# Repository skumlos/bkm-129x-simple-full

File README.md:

A full sized version of the BKM-129X compatible board

Revision D

Should be able to be created at ~$40, with the ADG1611BRUZ being the most expensive component.
Note that DG1411EEQ is pin-compatible with a slighly higher Ron.

This requires an Arduino Nano v3 *or* the ATMEGA328PB mounted, which is then loaded with the
latest BKM-129X-MCU code from https://github.com/skumlos/bkm-129x-mcu

The has 4 switches to be able to turn internal 75 Ohm termination on out pass signal through to the output BNCs. You 
can choose to set all switches down, and then terminate with external termination resistors. If you wish to omit the
switches altogther, bridge the two pins bottom left of each switch (when viewed component side, BNCs to left). 
A 0 Ohm 0805 should be able to reach here I guess.

Connections from top to bottom when viewing component side, with BNCs to the left:
               _______________________________________
            __| _                                     |
Y/G IN     |___|_|                                    |
            __| _                                     |
Y/G OUT    |___|_|                                   _|
            __| _                                   | |
B-Y/B IN   |___|_|                                  | |
            __| _                                   | |
B-Y/B OUT  |___|_|                                  | |
            __| _                                   | |
R-Y/R IN   |___|_|                                  | |
            __| _                                   | |
R-Y/R OUT  |___|_|                                  | |
            __| _                                   |_|
SYNC IN    |___|_|                                    |
            __| _                                     |
SYNC OUT   |___|_|                                    |
              |_______________________________________|

Just like the original BKM-129X.

For more information go to https://immerhax.com/?p=422

You are welcome to clone, produce and sell hardware based on this. Please keep changes and so on open source.

Cool kids give credit where due.

---------

Programming the onboard ATMEGA328PB is a little different than when using a pre-made Arduino board.
The reason for this is that the fuses of the ATMEGA aren't set when the MCU leaves the factory.
Thus to program it, you will need ATMEGA328PB support in the Arduino IDE. The easiest way is to
install the MiniCore board support package (through the Boards Manager), for installation
check the "How to install" at https://github.com/MCUdude/MiniCore.
When MiniCore is available,  select the ATMEGA328 under MiniCore in the board menu, then select
"External 16 MHz" in Clock, disable BOD, select ATMEGA328PB in Variant, select No bootloader.
Then press "Burn bootloader" (assuming your programmer and so on is already setup). This will
program the fuses. Last, upload the sketch by pressing "Upload using programmer". If you don't
do this, nothing will work, because the MCU won't know how to use the external clock and so on.

---------

Should be compatible with basically all monitors that accept the original BKM-129X

Check the MCU code for verified compatibility.

---------

Board revision history:

D: Change hole size in backplane connector to accomodate larger pin sizes,
   support 1117 LDOs, change to Kicad 5 footprints, general cleanup

C: Fixed THS7374 filter bypass.

B: Added onboard MCU option

A: Initial version

---------

Copyright © 2022 Martin Hejnfelt <martin@hejnfelt.com>
This work is free. You can redistribute it and/or modify it under the
terms of the Do What The Fuck You Want To Public License, Version 2,
as published by Sam Hocevar. See the LICENSE file for more details.

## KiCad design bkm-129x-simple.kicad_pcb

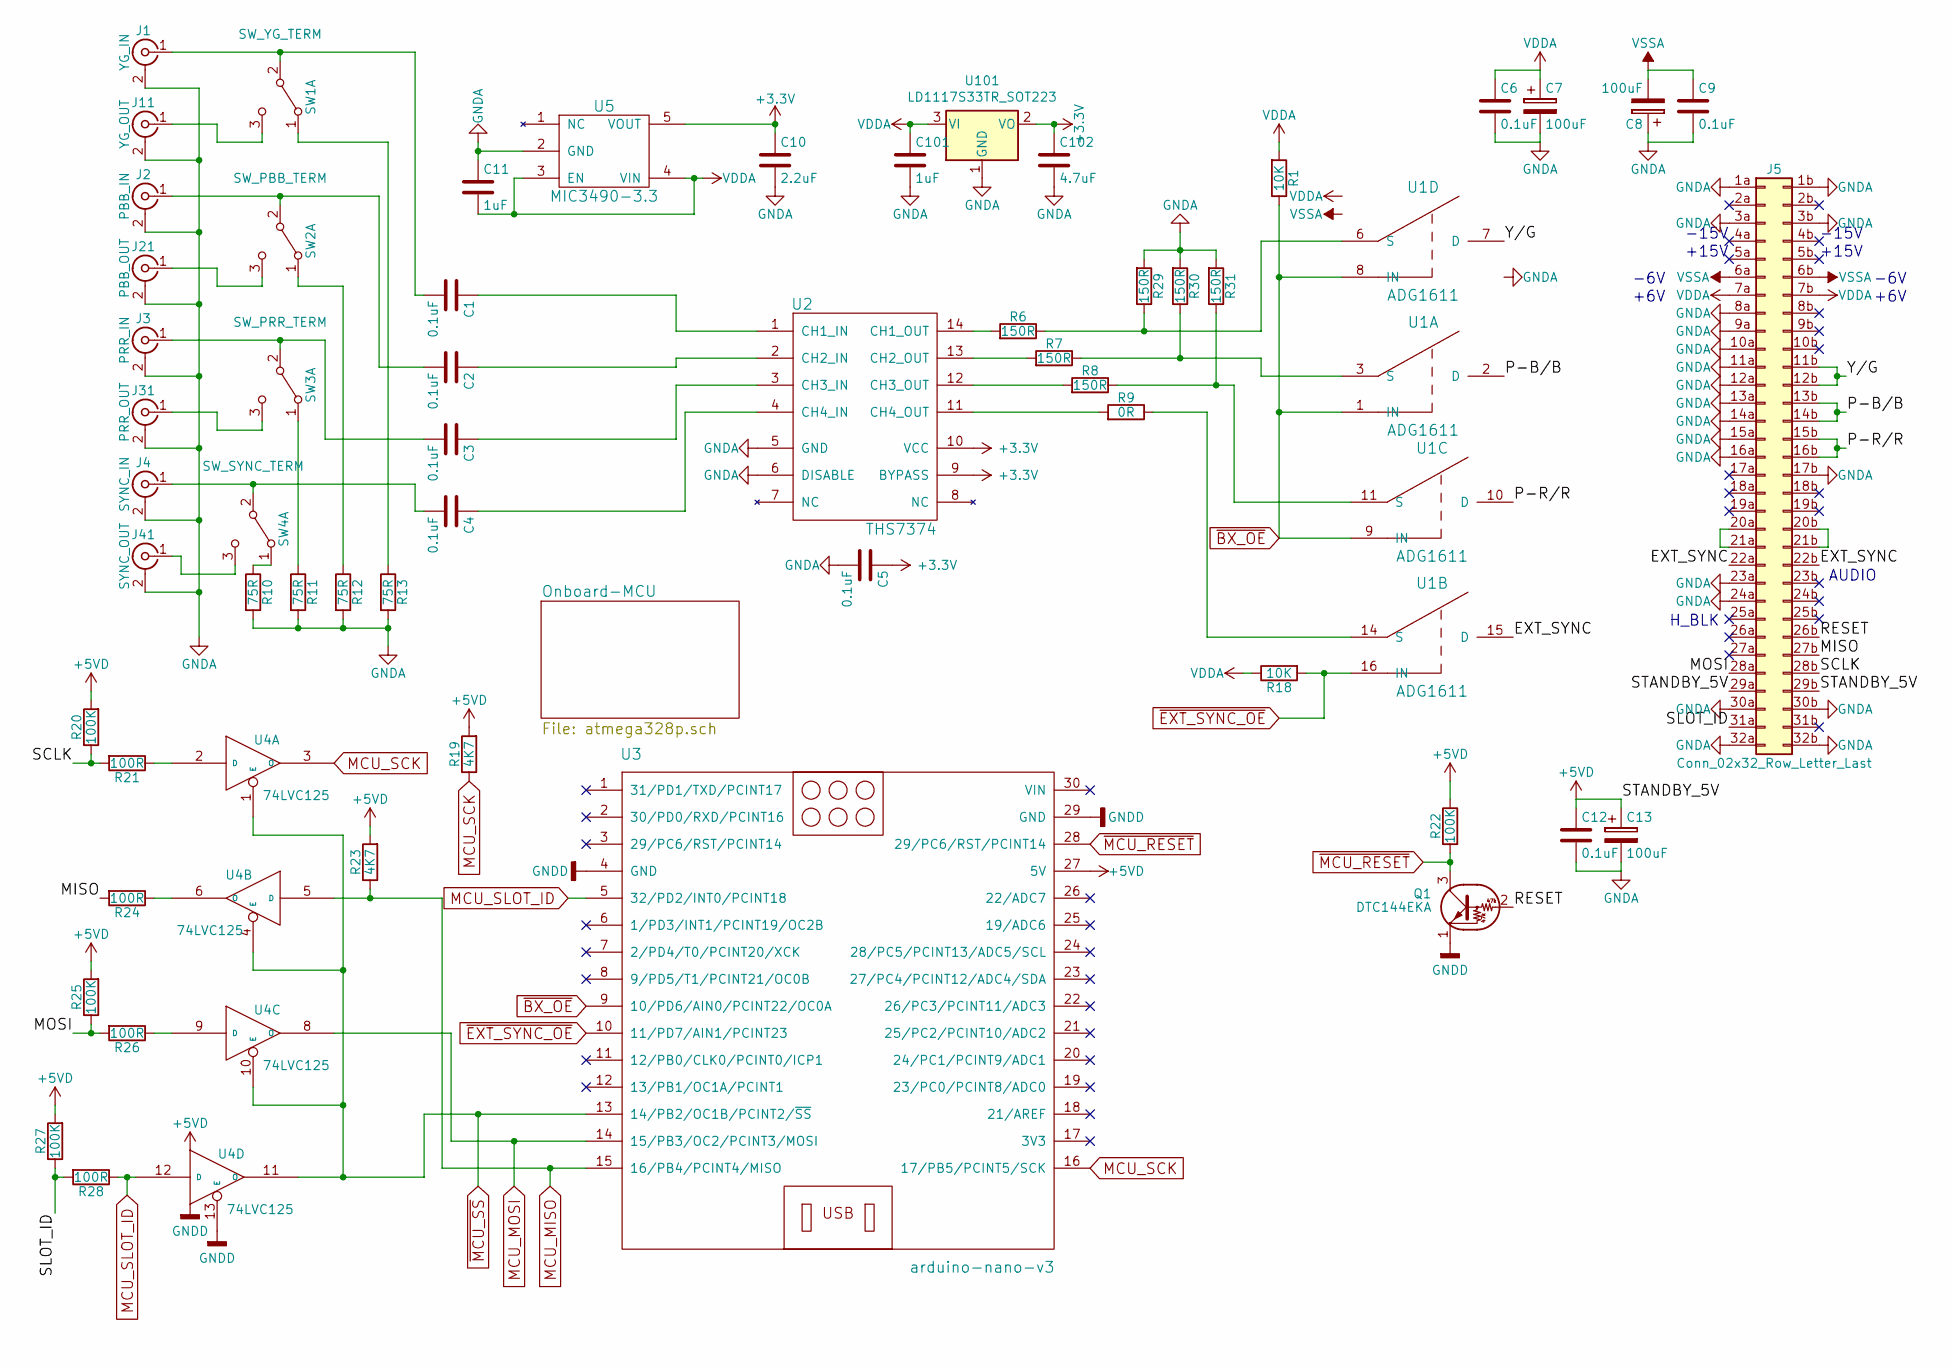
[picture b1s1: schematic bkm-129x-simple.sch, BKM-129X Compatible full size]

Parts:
C1, C2, C3, C4, C5, C6, C9, C12: 0.1uF; C_0805_2012Metric_Pad1.18x1.45mm_HandSolder
C7, C8, C13: 100uF; CP_Elec_6.3x5.3
C10: 2.2uF; C_0805_2012Metric_Pad1.18x1.45mm_HandSolder
C11, C101: 1uF; C_0805_2012Metric_Pad1.18x1.45mm_HandSolder
C102: 4.7uF; C_0805_2012Metric_Pad1.18x1.45mm_HandSolder
J1: YG_IN; BNC-THT
J2: PBB_IN; BNC-THT
J3: PRR_IN; BNC-THT
J4: SYNC_IN; BNC-THT
J5: Conn_02x32_Row_Letter_Last; STANDARD-PIN-64P-RA
J11: YG_OUT; BNC-THT
J21: PBB_OUT; BNC-THT
J31: PRR_OUT; BNC-THT
J41: SYNC_OUT; BNC-THT
Q1: DTC144EKA; SC-59_Handsoldering
R1, R18: 10K; R_0805_2012Metric_Pad1.20x1.40mm_HandSolder
R6, R7, R8, R29, R30, R31: 150R; R_0805_2012Metric_Pad1.20x1.40mm_HandSolder
R9: 0R; R_0805_2012Metric_Pad1.20x1.40mm_HandSolder
R10, R11, R12, R13: 75R; R_0805_2012Metric_Pad1.20x1.40mm_HandSolder
R19, R23: 4K7; R_0805_2012Metric_Pad1.20x1.40mm_HandSolder
R20, R22, R25, R27: 100K; R_0805_2012Metric_Pad1.20x1.40mm_HandSolder
R21, R24, R26, R28: 100R; R_0805_2012Metric_Pad1.20x1.40mm_HandSolder
SW1: SW_YG_TERM; JS202011SCQN
SW2: SW_PBB_TERM; JS202011SCQN
SW3: SW_PRR_TERM; JS202011SCQN
SW4: SW_SYNC_TERM; JS202011SCQN
U1: ADG1611; TSSOP-16_4.4x5mm_P0.65mm
U2: THS7374; TSSOP-14_4.4x5mm_P0.65mm
U3: arduino-nano-v3
U4: 74LVC125; TSSOP-14_4.4x5mm_P0.65mm
U5: MIC3490-3.3; SOT-23-5_HandSoldering
U101: LD1117S33TR_SOT223; SOT-223-3_TabPin2

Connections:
+3V3: C5.1, C10.1, C102.1, U2.9 (BYPASS), U2.10 (VCC), U5.5 (VOUT), U101.2 (VO)
+5VD: C12.1, C13.1, J5.29a, J5.29b, R19.2, R20.2, R22.1, R23.2, R25.2, R27.2, U3.27 (5V), U4.14 (VCC); also elsewhere on the board
/EXT_SYNC: J5.22a, J5.22b, U1.15 (D)
/MISO: J5.27b, R24.2
/MOSI: J5.28a, R25.1, R26.2
/P-B/B: J5.13b, J5.14b, U1.2 (D)
/P-R/R: J5.15b, J5.16b, U1.10 (D)
/RESET: J5.26b, Q1.2 (B)
/SCLK: J5.28b, R20.1, R21.2
/SLOT_ID: J5.31a, R27.1, R28.2
/Y/G: J5.11b, J5.12b, U1.7 (D)
MCU_MISO: R23.1, U3.15 (16/PB4/PCINT4/MISO), U4.5 (D); also elsewhere on the board
MCU_MOSI: U3.14 (15/PB3/OC2/PCINT3/MOSI), U4.8 (O); also elsewhere on the board
MCU_SCK: R19.1, U3.16 (17/PB5/PCINT5/SCK), U4.3 (O); also elsewhere on the board
MCU_SLOT_ID: R28.1, U3.5 (32/PD2/INT0/PCINT18), U4.12 (D); also elsewhere on the board
unnamed: C1.1, U2.1 (CH1_IN)
unnamed: C1.2, J1.1 (In), SW1.2 (B)
unnamed: C2.1, U2.2 (CH2_IN)
unnamed: C2.2, J2.1 (In), SW2.2 (B)
unnamed: C3.1, U2.3 (CH3_IN)
unnamed: C3.2, J3.1 (In), SW3.2 (B)
unnamed: C4.1, U2.4 (CH4_IN)
unnamed: C4.2, J4.1 (In), SW4.2 (B)
unnamed: J5.20a, J5.21a
unnamed: J5.20b, J5.21b
unnamed: J11.1 (In), SW1.3 (C)
unnamed: J21.1 (In), SW2.3 (C)
unnamed: J31.1 (In), SW3.3 (C)
unnamed: J41.1 (In), SW4.3 (C)
unnamed: R6.2, U2.14 (CH1_OUT)
unnamed: R7.2, U2.13 (CH2_OUT)
unnamed: R8.2, U2.12 (CH3_OUT)
unnamed: R9.1, U1.14 (S)
unnamed: R9.2, U2.11 (CH4_OUT)
unnamed: R10.1, SW4.1 (A)
unnamed: R11.1, SW3.1 (A)
unnamed: R12.1, SW2.1 (A)
unnamed: R13.1, SW1.1 (A)
unnamed: R21.1, U4.2 (D)
unnamed: R24.1, U4.6 (O)
unnamed: R26.1, U4.9 (D)
unnamed: R6.1, R29.1, U1.6 (S)
unnamed: R7.1, R30.1, U1.3 (S)
unnamed: R8.1, R31.1, U1.11 (S)
VDD: C6.1, C7.1, C11.2, C101.1, J5.7a, J5.7b, R1.2, R18.1, U1.13 (VDD), U5.3 (EN), U5.4 (VIN), U101.3 (VI)
VSS: C8.2, C9.1, J5.6a, J5.6b, U1.4 (VSS)
~BX_OE: R1.1, U1.1 (IN), U1.8 (IN), U1.9 (IN), U3.9 (10/PD6/AIN0/PCINT22/OC0A); also elsewhere on the board
~EXT_SYNC_OE: R18.2, U1.16 (IN), U3.10 (11/PD7/AIN1/PCINT23); also elsewhere on the board
~MCU_RESET: Q1.3 (C), R22.2, U3.28 (29/PC6/RST/PCINT14); also elsewhere on the board
~MCU_SS: U3.13 (14/PB2/OC1B/PCINT2/~SS), U4.1 (E), U4.4 (E), U4.10 (E), U4.11 (O); also elsewhere on the board

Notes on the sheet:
-15V
+15V
-6V
+6V
AUDIO
H_BLK

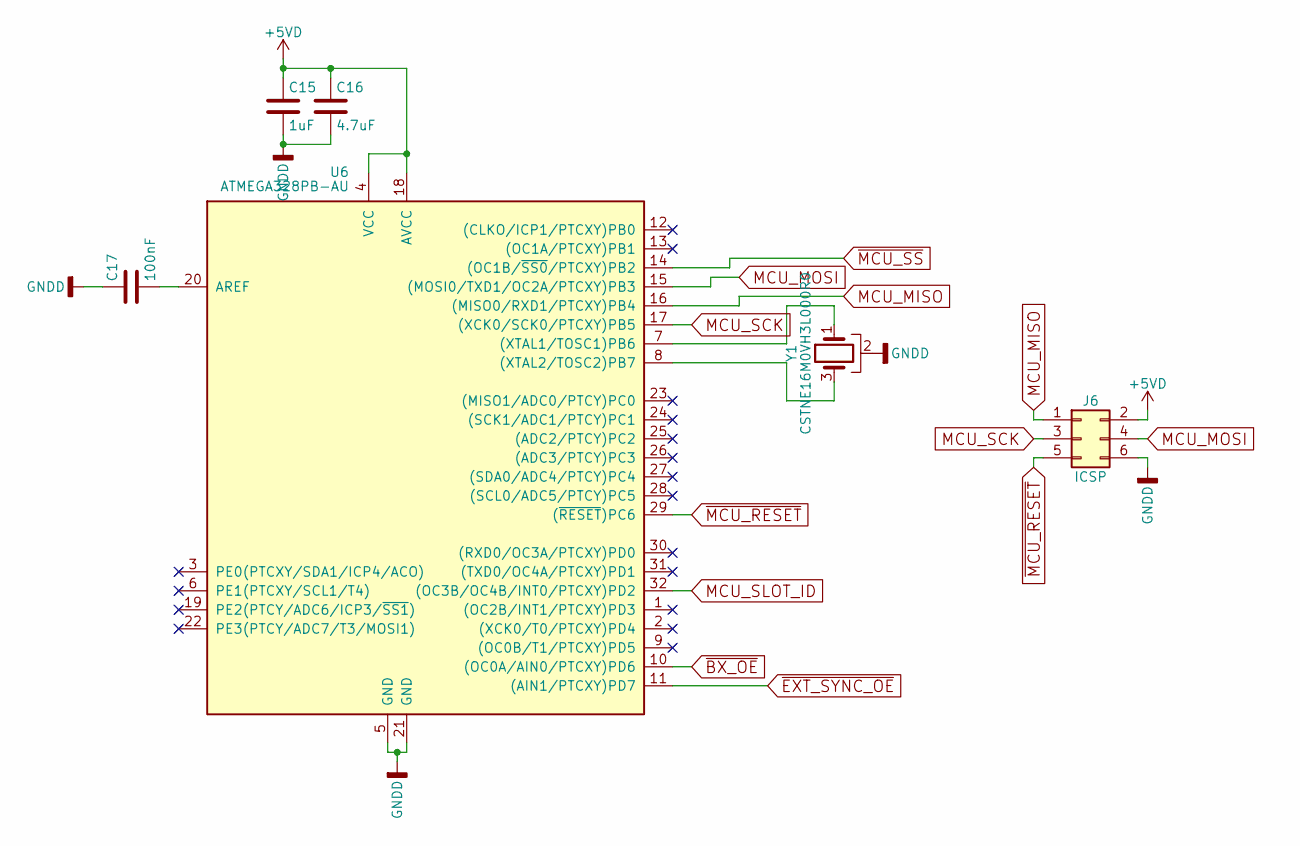
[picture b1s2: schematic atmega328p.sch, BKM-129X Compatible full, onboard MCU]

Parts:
C15: 1uF; C_0805_2012Metric_Pad1.18x1.45mm_HandSolder
C16: 4.7uF; C_0805_2012Metric_Pad1.18x1.45mm_HandSolder
C17: 100nF; C_0805_2012Metric_Pad1.18x1.45mm_HandSolder
J6: ICSP; Pin_Header_Straight_2x03_Pitch2.54mm
U6: ATMEGA328PB-AU; TQFP-32_7x7mm_P0.8mm
Y1: CSTNE16M0VH3L000R0; CSTNEx

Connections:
+5VD: C15.1, C16.1, J6.2, U6.4 (VCC), U6.18 (AVCC); also elsewhere on the board
MCU_MISO: J6.1, U6.16 ((MISO0/RXD1/PTCXY)PB4); also elsewhere on the board
MCU_MOSI: J6.4, U6.15 ((MOSI0/TXD1/OC2A/PTCXY)PB3); also elsewhere on the board
MCU_SCK: J6.3, U6.17 ((XCK0/SCK0/PTCXY)PB5); also elsewhere on the board
MCU_SLOT_ID: U6.32 ((OC3B/OC4B/INT0/PTCXY)PD2); also elsewhere on the board
unnamed: C17.2, U6.20 (AREF)
unnamed: U6.7 ((XTAL1/TOSC1)PB6), Y1.1
unnamed: U6.8 ((XTAL2/TOSC2)PB7), Y1.3
~BX_OE: U6.10 ((OC0A/AIN0/PTCXY)PD6); also elsewhere on the board
~EXT_SYNC_OE: U6.11 ((AIN1/PTCXY)PD7); also elsewhere on the board
~MCU_RESET: J6.5, U6.29 ((~RESET~)PC6); also elsewhere on the board
~MCU_SS: U6.14 ((OC1B/~SS0~/PTCXY)PB2); also elsewhere on the board

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
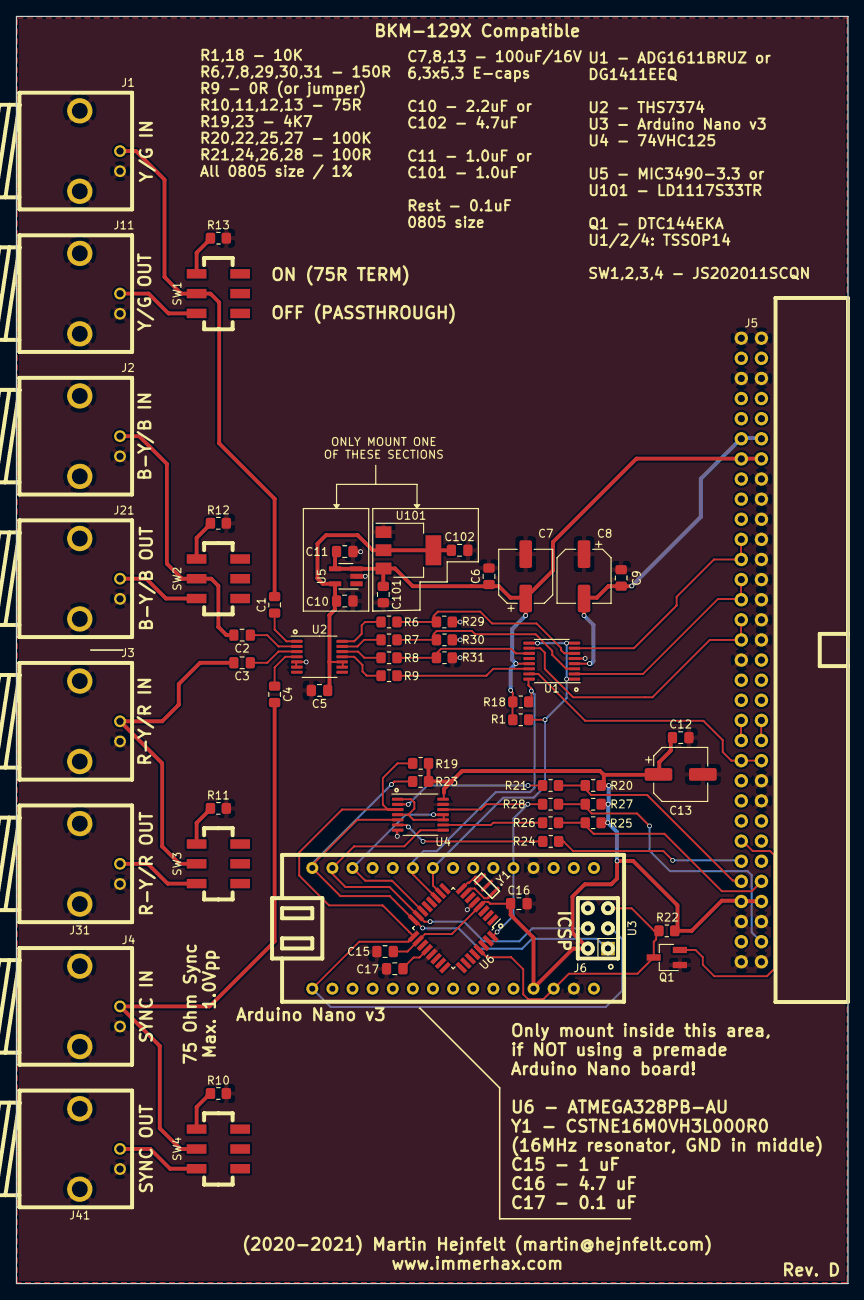
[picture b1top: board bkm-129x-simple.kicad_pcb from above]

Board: 2 copper layers, 105.0 x 160.0 mm, 64 parts (0 on the bottom side), 54 nets.

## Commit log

2020-06-28 Add sync level info
2020-07-28 Rev B: Added onboard MCU
2020-09-02 Add onboard ATMEGA328PB
2020-09-02 Added plot
2020-09-02 Added programming to readme
2021-04-18 Fixed the THS7374 filter stuff, moved to Kicad 5
2021-08-10 Add plot
2022-05-19 Revision D
